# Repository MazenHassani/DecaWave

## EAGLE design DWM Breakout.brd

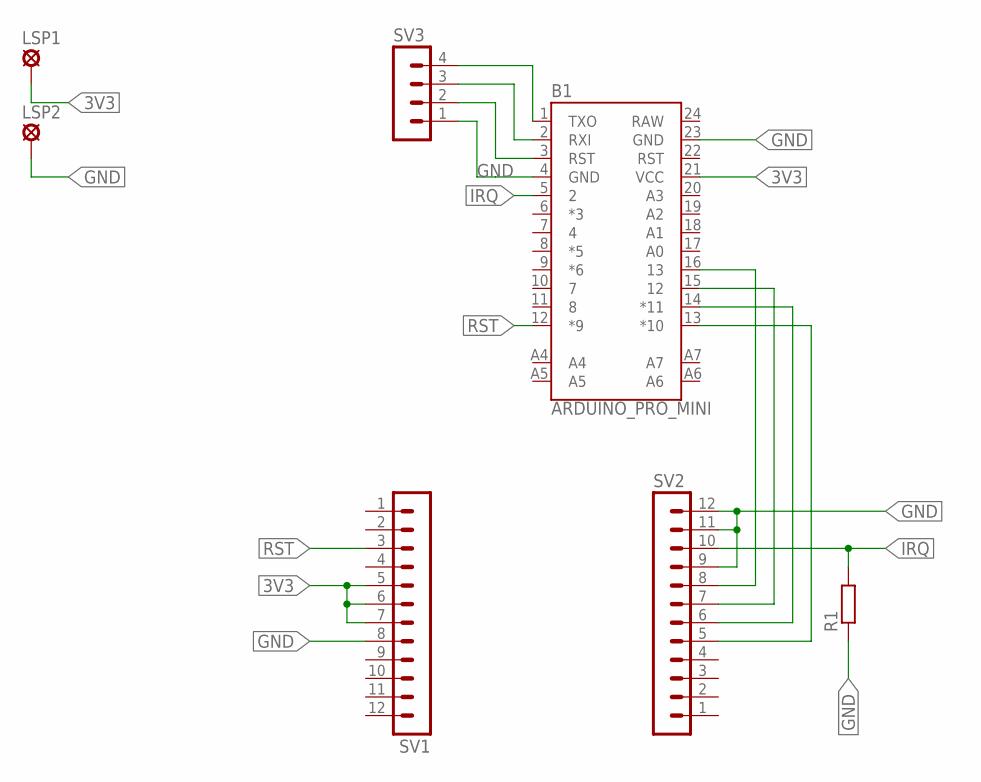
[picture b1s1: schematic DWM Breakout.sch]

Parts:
B1: ARDUINO_PRO_MINI
LSP1, LSP2: SE14
R1: R-EU_0207/10; 0207/10
SV1, SV2: MA12-1
SV3: MA04-1

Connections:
3V3: B1.21 (VCC), LSP1.MP, SV1.5, SV1.6, SV1.7
GND: B1.4 (GND), B1.23 (GND), LSP2.MP, R1.1, SV1.8, SV2.9, SV2.11, SV2.12, SV3.1
IRQ: B1.5 (2), R1.2, SV2.10
unnamed: B1.15 (12), SV2.7
unnamed: B1.1 (TXO), SV3.4
unnamed: B1.16 (13), SV2.8
unnamed: B1.14 (*11), SV2.6
unnamed: B1.13 (*10), SV2.5
unnamed: B1.2 (RXI), SV3.3
unnamed: B1.3 (RST), SV3.2
RAW: B1.24 (RAW)
RST: B1.12 (*9), SV1.3

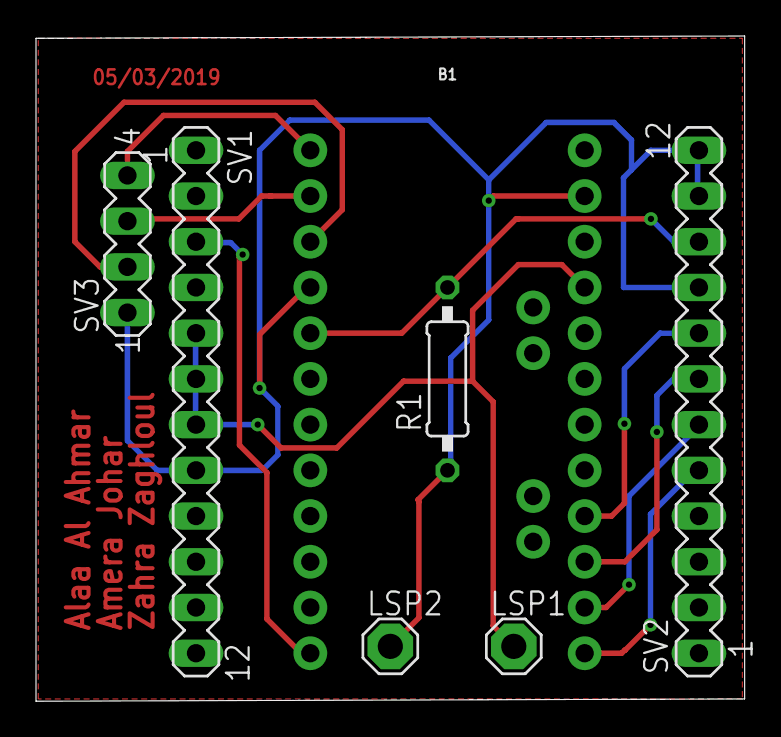
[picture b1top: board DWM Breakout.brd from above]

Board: 2 copper layers, 39.4 x 37.0 mm, 7 parts (0 on the bottom side), 11 nets.

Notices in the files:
parts and their libraries:
SparkFun-Boards: Licensing: Creative Commons ShareAlike 4.0 International - https://creativecommons.org/licenses/by-sa/4.0
